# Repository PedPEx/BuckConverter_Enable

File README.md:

# BuckConverter with Enable Input (WIP!)

A BuckConverter based on the [Texas Instruments LM33630](https://www.ti.com/product/LMR33630). By default the converter is set to an output voltage of 5V and enabled permanently. Avaliable output levels are 3.3 V, 5 V, 9 V and 12 V. In order to select the desired output, only the corresponding `Rsel` 0 ohm resistor/connection has to be installed. 

The external enable input is enabled by cutting the builtin connection in `J1` and connectiong the solder bridge in the other direction. 

It's possible to use a [Weidmüller 1824460000 - LSF-SMT 3.50/06/90 3.5SN BK TU](https://catalog.weidmueller.com/catalog/Start.do?ObjectID=1824460000), a [PhoenixContact 1861975 - SPTAF 1 6-3,5-IL](https://www.phoenixcontact.com/de-de/produkte/leiterplattenklemme-sptaf-1-6-35-il-1861975) or a [screw terminal block from LCSC](https://www.lcsc.com/product-detail/Screw-Terminal-Blocks_DORABO-DB127S-3-5-6P-GN-S_C2997513.html) for J1. A standard 3.5 mm pitch pin header is also possible.

[Online BOM](https://htmlpreview.github.io/?https://raw.githubusercontent.com/PedPEx/BuckConverter_Enable/master/bom/webviewer-BOM.html)

---
**Note**

The pictures were rendered with the help of Blender and the [pcb2blender](https://github.com/30350n/pcb2blender) plugin and the HTML BOM was created withwith [InteractiveHtmlBom](https://github.com/openscopeproject/InteractiveHtmlBom).

---

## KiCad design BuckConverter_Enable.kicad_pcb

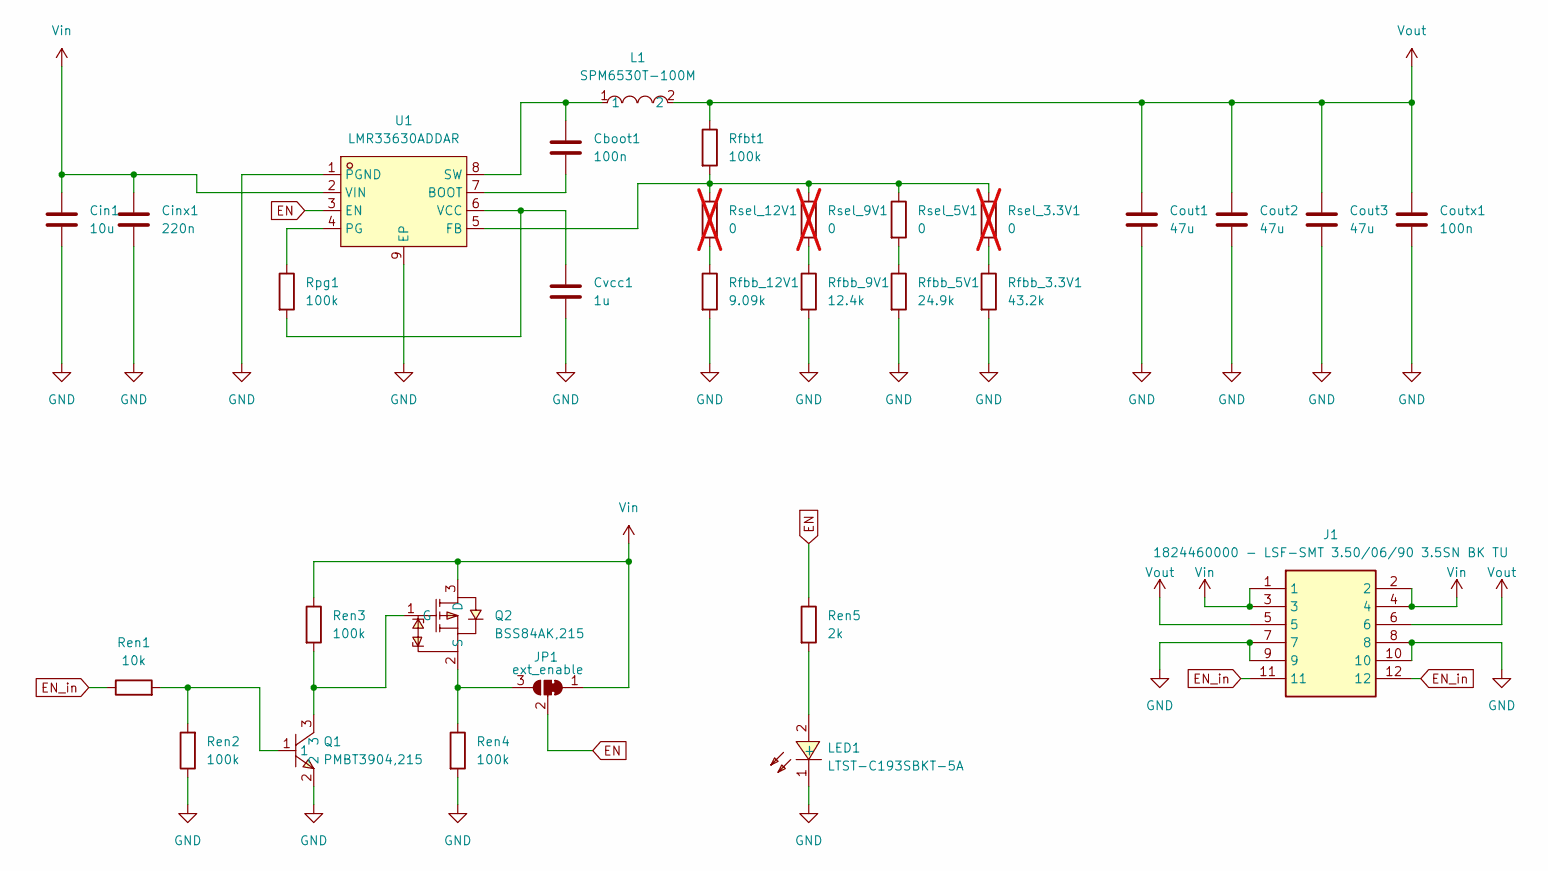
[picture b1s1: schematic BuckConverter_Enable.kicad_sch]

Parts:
Cboot1: 100n; C_0603_1608Metric
Cin1: 10u; C_1210_3225Metric
Cinx1: 220n; C_0805_2012Metric
Cout1, Cout2, Cout3: 47u; C_1206_3216Metric
Coutx1: 100n; C_0603_1608Metric
Cvcc1: 1u; C_0603_1608Metric
J1: 1824460000 - LSF-SMT 3.50/06/90 3.5SN BK TU; 1824460000 - LSF-SMT 3.500690 3.5SN BK TU; Manufacturer_Part_Number 1824460000; Mouser Part Number 470-1824460000
JP1: ext_enable; SolderJumper-3_P1.3mm_Bridged12_RoundedPad1.0x1.5mm
L1: SPM6530T-100M; IND-SMD_L7.1-W6.6; LCSC Part C112288
LED1: LTST-C193SBKT-5A; LED0603-RD_BLUE; LCSC Part C364558
Q1: PMBT3904,215; SOT-23_L2.9-W1.3-P1.90-LS2.4-BR; LCSC Part C8667
Q2: BSS84AK,215; SOT-23_L2.9-W1.3-P1.90-LS2.4-BR; LCSC Part C127273
Ren1: 10k; C_0603_1608Metric
Ren2, Ren3, Ren4: 100k; C_0603_1608Metric
Ren5: 2k; C_0603_1608Metric
Rfbb_3.3V1: 43.2k; C_0603_1608Metric
Rfbb_5V1: 24.9k; C_0603_1608Metric
Rfbb_9V1: 12.4k; C_0603_1608Metric
Rfbb_12V1: 9.09k; C_0603_1608Metric
Rfbt1: 100k; C_0603_1608Metric
Rpg1: 100k; C_0603_1608Metric
Rsel_3.3V1, Rsel_9V1, Rsel_12V1: 0; C_0603_1608Metric; not fitted
Rsel_5V1: 0; C_0603_1608Metric
U1: LMR33630ADDAR; ESOP-8_L4.9-W3.9-P1.27-LS6.0-TL-EP; LCSC Part C841384

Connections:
EN: JP1.2 (C), Ren5.1, U1.3 (EN)
EN_in: J1.11, J1.12, Ren1.1; also elsewhere on the board
GND: Cin1.2, Cinx1.2, Cout1.2, Cout2.2, Cout3.2, Coutx1.2, Cvcc1.2, J1.7, J1.8, J1.9, J1.10, LED1.1 (-), Q1.2, Ren2.1, Ren4.2, Rfbb_3.3V1.2, Rfbb_5V1.2, Rfbb_9V1.2, Rfbb_12V1.2, U1.1 (PGND), U1.9 (EP); also elsewhere on the board
unnamed: JP1.3 (B), Q2.2 (S), Ren4.1
unnamed: LED1.2 (+), Ren5.2
unnamed: Q1.1, Ren1.2, Ren2.2
unnamed: Q1.3, Q2.1 (G), Ren3.2
unnamed: Rfbb_3.3V1.1, Rsel_3.3V1.2
unnamed: Rfbb_5V1.1, Rsel_5V1.2
unnamed: Rfbb_9V1.1, Rsel_9V1.2
unnamed: Rfbb_12V1.1, Rsel_12V1.2
unnamed: Cboot1.2, U1.7 (BOOT)
unnamed: Rfbt1.2, Rsel_3.3V1.1, Rsel_5V1.1, Rsel_9V1.1, Rsel_12V1.1, U1.5 (FB)
unnamed: Rpg1.1, U1.4 (PG)
unnamed: Cboot1.1, L1.1, U1.8 (SW)
unnamed: Cvcc1.1, Rpg1.2, U1.6 (VCC)
Vin: Cin1.1, Cinx1.1, J1.1, J1.2, J1.3, J1.4, JP1.1 (A), Q2.3 (D), Ren3.1, U1.2 (VIN); also elsewhere on the board
Vout: Cout1.1, Cout2.1, Cout3.1, Coutx1.1, J1.5, J1.6, L1.2, Rfbt1.1; also elsewhere on the board

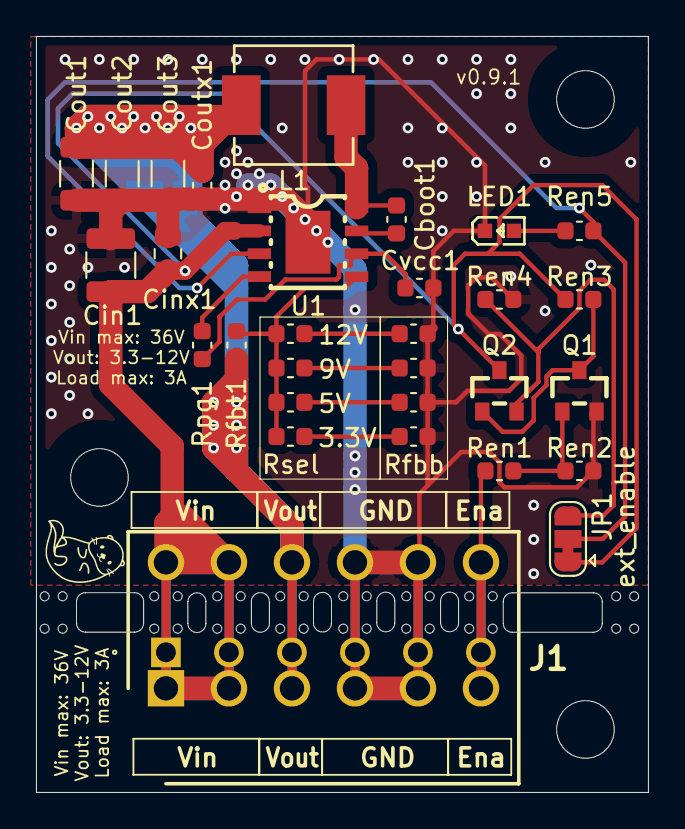
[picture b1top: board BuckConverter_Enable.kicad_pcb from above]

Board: 2 copper layers, 34.0 x 42.0 mm, 31 parts (0 on the bottom side), 18 nets.

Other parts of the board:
J**: 1861975 - SPTAF 1 6-3,5-IL

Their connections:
EN_in: J**.11, J**.12; also elsewhere on the board
GND: J**.7, J**.8, J**.9, J**.10; also elsewhere on the board
Vin: J**.1, J**.2, J**.3, J**.4; also elsewhere on the board
Vout: J**.5, J**.6; also elsewhere on the board

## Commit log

2024-08-13 init
2024-08-13 fixed link

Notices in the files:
BuckConverter_Enable.kicad_pcb:
©PedPEx
